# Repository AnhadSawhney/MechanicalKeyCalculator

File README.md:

# MechanicalKeyCalculator
These are the CAD files for a calculator with mechanical keyswitches.

The board folder contains all of the EDA files made with kicad.

The 3dModel folder contains all of the CAD files for the board made with openSCAD.

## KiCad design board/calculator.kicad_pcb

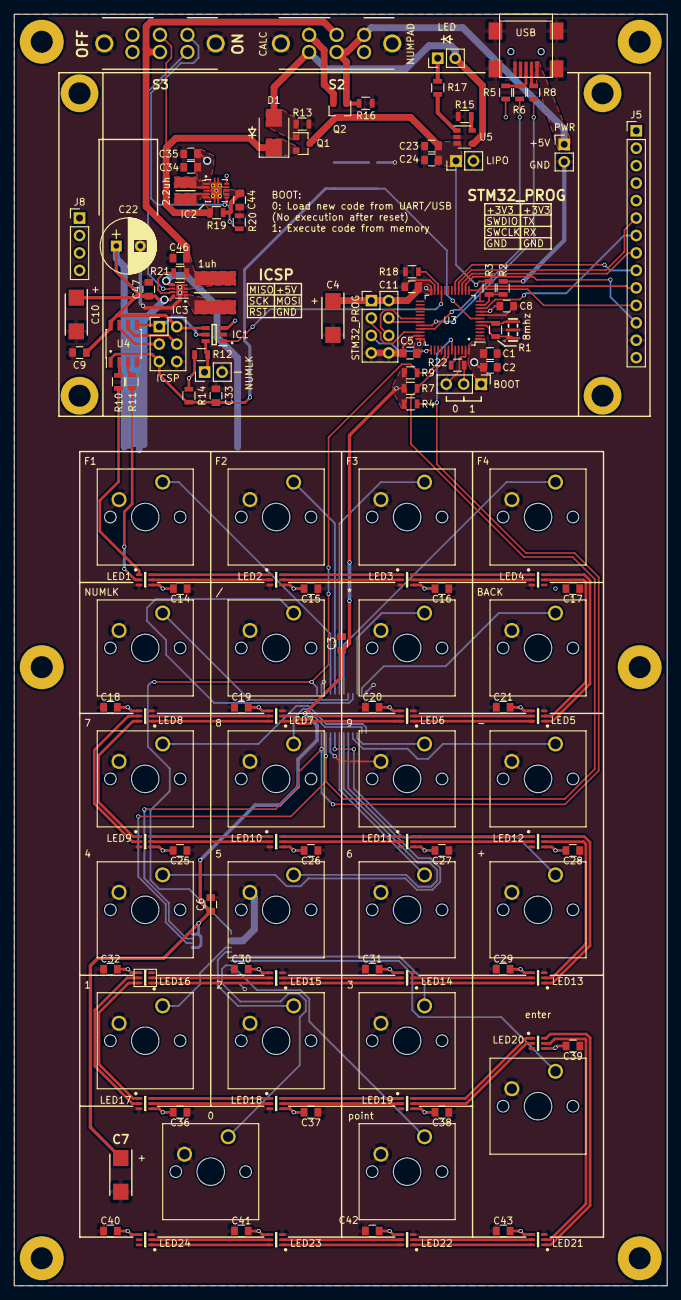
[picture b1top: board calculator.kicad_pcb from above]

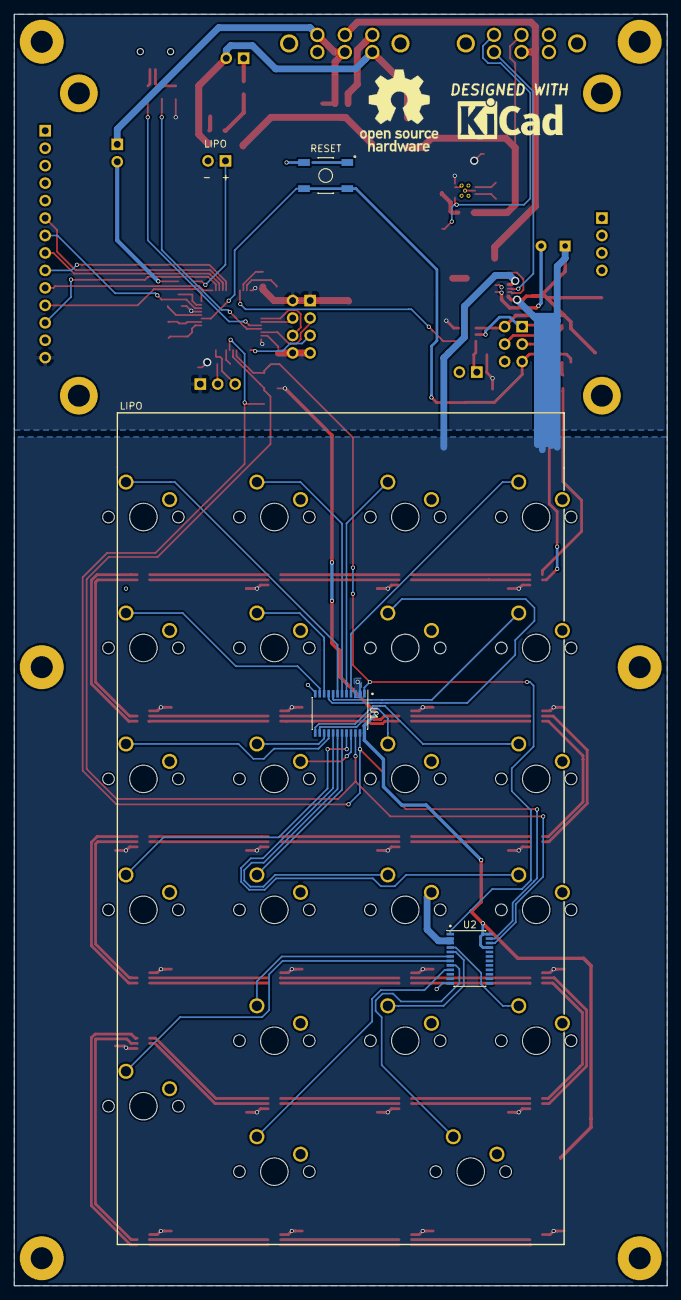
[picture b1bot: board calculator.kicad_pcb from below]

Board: 2 copper layers, 95.0 x 185.0 mm, 139 parts (3 on the bottom side), 121 nets.

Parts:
8mhz: 8mhz; CSTCE12M0G55-R0
BOOT: BOOT; Pin_Header_Straight_1x03_Pitch2.54mm
C1, C46: 4.7uf; C_0805
C2, C3, C5, C6, C8, C9, C11, C14, C15, C16, C17, C18, C19, C20, C21, C25, C26, C27, C28, C29, C30, C31, C32, C36, C37, C38, C39, C40, C41, C42, C43, C44: 0.1uf; C_0805
C4, C7, C10: 100uf; CAPPM6032X280N
C22: 1000uf; CP_Radial_D8.0mm_P3.50mm
C23, C34, C35: 10uf; C_0805
C24, C33: 1uf; C_0805
C47: 22uf; C_0805
D1: D_Schottky; D_SMB
IC1: PI4ULS5V201TAEX; SOT95P280X115-6N
IC2: TPS63001DRCR; VSON-10-1EP_3x3mm_Pitch0.5mm_ThermalPad
IC3: MIC2876-5.5YMT-T5; DFN-8-1EP_2x2mm_Pitch0.5mm
ICSP: ICSP; Pin_Header_Straight_2x03_Pitch2.54mm
J5: TFT; Socket_Strip_Straight_1x14_Pitch2.54mm
J8: SD; Socket_Strip_Straight_1x04_Pitch2.54mm
L1: 2.2uh; INDC3030X120N
L2: 1uh
LED: LED; Pin_Header_Straight_1x02_Pitch2.54mm
LED1, LED2, LED3, LED4, LED5, LED6, LED7, LED8, LED9, LED10, LED11, LED12, LED13, LED14, LED15, LED16, LED17, LED18, LED19, LED20, LED21, LED22, LED23, LED24: APA102; SON75P200X200X100-6N
LIPO: LIPO; Pin_Header_Straight_1x02_Pitch2.54mm
NUMLK: NUMLK; Pin_Header_Straight_1x02_Pitch2.54mm
PWR: Socket_Strip_Straight_1x02_Pitch2.54mm
Q1, Q2: DMP1045U; SOT-23
R1, R21: 1m; R_0805
R2: 33k; R_0805
R3, R4, R7, R9, R12, R14, R18, R20: 10k; R_0805
R5: 1.5k; R_0805
R6, R8: 22; R_0805
R10, R11: 470; R_0805
R13, R16, R22: 100k; R_0805
R15: 4.7k; R_0805
R17: 220; R_0805
R19: 100; R_0805
S1: RESET; SW_TL3342F160QG
S2, S3: DPDT; MFS201N-16-Z
STM32_PROG: STM32_PROG; Pin_Header_Straight_2x04_Pitch2.54mm
SW1: F1; SW_Cherry_MX1A_1.00u_PCB
SW2: 1; SW_Cherry_MX1A_1.00u_PCB
SW3: F2; SW_Cherry_MX1A_1.00u_PCB
SW4: 2; SW_Cherry_MX1A_1.00u_PCB
SW5: F3; SW_Cherry_MX1A_1.00u_PCB
SW6: 3; SW_Cherry_MX1A_1.00u_PCB
SW7: F4; SW_Cherry_MX1A_1.00u_PCB
SW8: enter; SW_Cherry_MX1A_2.00u_Vertical_PCB
SW9: NUMLK; SW_Cherry_MX1A_1.00u_PCB
SW10: 0; SW_Cherry_MX1A_2.00u_PCB
SW11: /; SW_Cherry_MX1A_1.00u_PCB
SW12: point; SW_Cherry_MX1A_1.00u_PCB
SW13: *; SW_Cherry_MX1A_1.00u_PCB
SW14: BACK; SW_Cherry_MX1A_1.00u_PCB
SW15: 7; SW_Cherry_MX1A_1.00u_PCB
SW16: 8; SW_Cherry_MX1A_1.00u_PCB
SW17: 9; SW_Cherry_MX1A_1.00u_PCB
SW18: -; SW_Cherry_MX1A_1.00u_PCB
SW19: 4; SW_Cherry_MX1A_1.00u_PCB
SW20: 5; SW_Cherry_MX1A_1.00u_PCB
SW21: 6; SW_Cherry_MX1A_1.00u_PCB
SW22: +; SW_Cherry_MX1A_1.00u_PCB
U1, U2: TCA9555PWR; TSSOP-24_4.4x7.8mm_Pitch0.65mm
U3: STM32F103C8T6; LQFP-48_7x7mm_Pitch0.5mm
U4: ATTINY85-20SU; SOIC-8_3.9x4.9mm_Pitch1.27mm
U5: MCP73831; SOT-23-5
USB: USB_MINI_B; USB_Mini-B

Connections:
+3V3: BOOT.1, C1.2, C2.2, C3.1, C4.1, C5.1, C6.1, C7.1, C8.1, C11.1, C34.2, C35.1, IC1.3, IC2.1, IC2.10, J5.14, R4.2, R5.1, R7.2, R9.2, R12.2, R14.1, STM32_PROG.1, STM32_PROG.2, U1.24, U2.21, U2.24, U3.1, U3.9, U3.24, U3.36, U3.48
+5V: C9.1, C10.1, C14.2, C15.2, C16.2, C17.2, C18.2, C19.2, C20.2, C21.2, C22.1, C25.2, C26.2, C27.2, C28.2, C29.2, C30.2, C31.2, C32.2, C36.2, C37.2, C38.2, C39.2, C40.2, C41.2, C42.2, C43.2, C47.1, IC1.4, IC3.5, IC3.8, ICSP.2, LED1.4, LED2.4, LED3.4, LED4.4, LED5.4, LED6.4, LED7.4, LED8.4, LED9.4, LED10.4, LED11.4, LED12.4, LED13.4, LED14.4, LED15.4, LED16.4, LED17.4, LED18.4, LED19.4, LED20.4, LED21.4, LED22.4, LED23.4, LED24.4, U4.8
/BOOT: R22.2, U3.44
/CHG_IN: D1.2, LED.2, Q1.1, R13.1, S2.6, U5.4
/CS: J5.12, U3.14
/D+: R6.2, U3.33
/D-: R8.2, U3.32
/D/C: J5.10, U3.13
/INT: R9.1, U1.1, U2.1, U3.41
/LED: J5.7, U3.10
/LED_C: R11.2, U4.3
/LED_D: R10.2, U4.2
/LIPO_RAW: C23.1, C24.1, LIPO.1, Q1.3, Q2.3, R3.1, U5.3
/MISO: IC1.5, ICSP.1, U4.5
/MODE: R18.2, S2.4, U3.22
/MOSI: ICSP.4, U4.6
/PROG_RX: STM32_PROG.6, U3.30
/PROG_TX: STM32_PROG.4, U3.31
/REG_VCC3: D1.1, IC2.5, Q1.2, R19.2, S3.2
/REG_VCC5: C46.1, IC3.3, L2.1, R21.2, S2.2, S3.5
/RST: C33.2, ICSP.5, R14.2, S1.3, S1.4, U3.7, U4.1
/SCK: ICSP.3, U4.7
/SCL: R7.1, U1.22, U2.22, U3.42
/SDA: R4.1, U1.23, U2.23, U3.43
/SWCLK: STM32_PROG.5, U3.37
/SWDIO: STM32_PROG.3, U3.34
/T_MISO: J5.6, U3.16
/T_MOSI: J5.9, U3.17
/T_RST: J5.11, U3.12
/T_SCK: J5.8, U3.15
/VBUS: PWR.1, Q2.1, R16.2, S2.1, S2.5, USB.1
GND: 8mhz.2, BOOT.3, C1.1, C2.1, C3.2, C4.2, C5.2, C6.2, C7.2, C8.2, C9.2, C10.2, C11.2, C14.1, C15.1, C16.1, C17.1, C18.1, C19.1, C20.1, C21.1, C22.2, C23.2, C24.2, C25.1, C26.1, C27.1, C28.1, C29.1, C30.1, C31.1, C32.1, C33.1, C34.1, C35.2, C36.1, C37.1, C38.1, C39.1, C40.1, C41.1, C42.1, C43.1, C44.2, C46.2, C47.2, IC1.2, IC2.3, IC2.9, IC2.11, IC3.2, IC3.4, IC3.9, ICSP.6, J5.13, LED1.3, LED2.3, LED3.3, LED4.3, LED5.3, LED6.3, LED7.3, LED8.3, LED9.3, LED10.3, LED11.3, LED12.3, LED13.3, LED14.3, LED15.3, LED16.3, LED17.3, LED18.3, LED19.3, LED20.3, LED21.3, LED22.3, LED23.3, LED24.3, LIPO.2, NUMLK.2, PWR.2, R2.2, R13.2, R15.1, R16.1, R18.1, R20.1, S1.1, S1.2, S2.7, S2.8, S3.7, S3.8, STM32_PROG.7, STM32_PROG.8, SW1.2, SW2.2, SW3.2, SW4.2, SW5.2, SW6.2, SW7.2, SW8.2, SW9.2, SW10.2, SW11.2, SW12.2, SW13.2, SW14.2, SW15.2, SW16.2, SW17.2, SW18.2, SW19.2, SW20.2, SW21.2, SW22.2, U1.2, U1.3, U1.12, U1.21, U2.2, U2.3, U2.12, U3.8, U3.20, U3.23, U3.35, U3.47, U4.4, U5.2, USB.5, USB.6
unnamed: C44.1, IC2.7, IC2.8, R19.1
unnamed: IC1.1, U3.21
unnamed: IC1.6, NUMLK.1, R12.1
unnamed: IC2.2, L1.1
unnamed: IC2.4, L1.2
unnamed: IC2.6, R20.2, S3.1
unnamed: IC3.1, L2.2
unnamed: IC3.6, S3.4
unnamed: IC3.7, R21.1
unnamed: R8.1, USB.2
unnamed: R5.2, R6.1, USB.3
unnamed: BOOT.2, R22.1
unnamed: LED.1, R17.2
unnamed: LED1.1, R10.1
unnamed: LED1.2, R11.1
unnamed: LED1.5, LED2.2
unnamed: LED1.6, LED2.1
unnamed: LED2.5, LED3.2
unnamed: LED2.6, LED3.1
unnamed: LED3.5, LED4.2
unnamed: LED3.6, LED4.1
unnamed: LED4.5, LED5.2
unnamed: LED4.6, LED5.1
unnamed: LED5.5, LED6.2
unnamed: LED5.6, LED6.1
unnamed: LED6.5, LED7.2
unnamed: LED6.6, LED7.1
unnamed: LED7.5, LED8.2
unnamed: LED7.6, LED8.1
unnamed: LED8.5, LED9.2
unnamed: LED8.6, LED9.1
unnamed: LED9.6, LED10.1
unnamed: LED9.5, LED10.2
unnamed: LED10.5, LED11.2
unnamed: LED10.6, LED11.1
unnamed: LED11.5, LED12.2
unnamed: LED11.6, LED12.1
unnamed: LED12.5, LED13.2
unnamed: LED12.6, LED13.1
unnamed: LED13.5, LED14.2
unnamed: LED13.6, LED14.1
unnamed: LED14.5, LED15.2
unnamed: LED14.6, LED15.1
unnamed: LED15.5, LED16.2
unnamed: LED15.6, LED16.1
unnamed: LED16.5, LED17.2
unnamed: LED16.6, LED17.1
unnamed: LED17.5, LED18.2
unnamed: LED17.6, LED18.1
unnamed: LED18.5, LED19.2
unnamed: LED18.6, LED19.1
unnamed: LED19.5, LED20.2
unnamed: LED19.6, LED20.1
unnamed: LED20.5, LED21.2
unnamed: LED20.6, LED21.1
unnamed: LED21.5, LED22.2
unnamed: LED21.6, LED22.1
unnamed: LED22.5, LED23.2
unnamed: LED22.6, LED23.1
unnamed: LED23.5, LED24.2
unnamed: LED23.6, LED24.1
unnamed: Q2.2, S2.3
unnamed: 8mhz.3, R1.1, U3.6
unnamed: 8mhz.1, R1.2, U3.5
unnamed: R2.1, R3.2, U3.11
unnamed: R15.2, U5.5
unnamed: R17.1, U5.1
unnamed: SW1.1, U1.4
unnamed: SW2.1, U2.4
unnamed: SW3.1, U1.5
unnamed: SW4.1, U2.5
unnamed: SW5.1, U1.6
unnamed: SW6.1, U2.6
unnamed: SW7.1, U1.7
unnamed: SW8.1, U2.7
unnamed: SW9.1, U1.8
unnamed: SW10.1, U2.8
unnamed: SW11.1, U1.9
unnamed: SW12.1, U2.9
unnamed: SW13.1, U1.10
unnamed: SW14.1, U1.11
unnamed: SW15.1, U1.13
unnamed: SW16.1, U1.14
unnamed: SW17.1, U1.15
unnamed: SW18.1, U1.16
unnamed: SW19.1, U1.17
unnamed: SW20.1, U1.18
unnamed: SW21.1, U1.19
unnamed: SW22.1, U1.20
